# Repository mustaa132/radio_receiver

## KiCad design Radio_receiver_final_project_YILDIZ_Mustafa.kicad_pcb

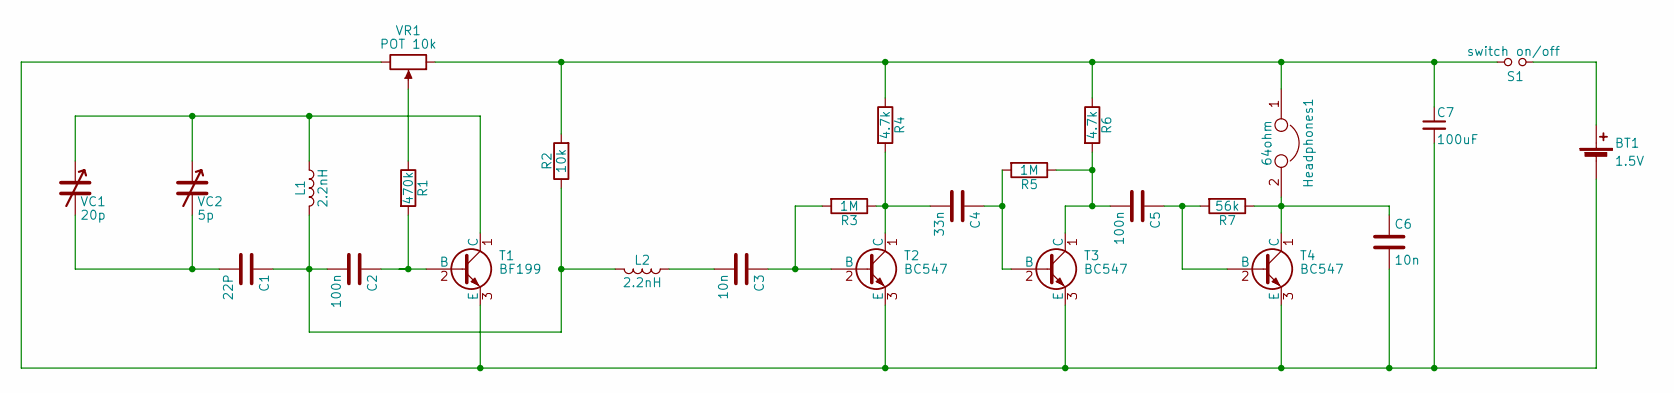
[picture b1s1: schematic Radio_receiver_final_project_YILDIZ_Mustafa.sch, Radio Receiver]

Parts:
BT1: 1.5V; WireConnection_2.50mmDrill
C1: 22P; C_1210_HandSoldering
C2: 100n; C_1206
C3, C6: 10n; C_Disc_D7.0mm_W2.5mm_P5.00mm
C4: 33n; C_Rect_L4.6mm_W3.0mm_P2.50mm_MKS02_FKP02
C5: 100n; C_Rect_L10.0mm_W3.0mm_P7.50mm_FKS3_FKP3
C7: 100uF; CP_Radial_D7.5mm_P2.50mm
Headphones1: 64ohm; RV_Disc_D7_W4_P5
L1, L2: 2.2nH; Neosid_Inductor_SM-PIC0602H
R1: 470k; R_Axial_DIN0309_L9.0mm_D3.2mm_P12.70mm_Horizontal
R2: 10k; R_Axial_DIN0207_L6.3mm_D2.5mm_P10.16mm_Horizontal
R3, R5: 1M; R_Axial_DIN0207_L6.3mm_D2.5mm_P10.16mm_Horizontal
R4, R6: 4.7k; R_Axial_DIN0207_L6.3mm_D2.5mm_P10.16mm_Horizontal
R7: 56k; R_Axial_DIN0207_L6.3mm_D2.5mm_P10.16mm_Horizontal
S1: switch on/off; WireConnection_1.50mmDrill
T1: BF199; TO-92_Molded_Narrow_Oval
T2, T4: BC547; TO-92_Molded_Narrow_Oval
T3: BC547; TO-92_Molded_Narrow
VC1: 20p; CP_Radial_Tantal_D4.5mm_P5.00mm
VC2: 5p; CP_Radial_Tantal_D5.0mm_P2.50mm
VR1: POT 10k; Potentiometer_Alps_RK097_Single_Vertical

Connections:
unnamed: BT1.1 (+), S1.1
unnamed: BT1.2 (-), C6.2, C7.2, T1.3 (E), T2.3 (E), T3.3 (E), T4.3 (E), VR1.3
unnamed: C1.1, C2.2, L1.2, L2.2, R2.1
unnamed: C1.2, VC1.2, VC2.2
unnamed: C2.1, R1.2, T1.2 (B)
unnamed: C3.1, R3.2, T2.2 (B)
unnamed: C3.2, L2.1
unnamed: C4.1, R5.2, T3.2 (B)
unnamed: C4.2, R3.1, R4.2, T2.1 (C)
unnamed: C5.1, R7.2, T4.2 (B)
unnamed: C5.2, R5.1, R6.2, T3.1 (C)
unnamed: C6.1, Headphones1.2, R7.1, T4.1 (C)
unnamed: C7.1, Headphones1.1, R2.2, R4.1, R6.1, S1.2, VR1.1
unnamed: L1.1, T1.1 (C), VC1.1, VC2.1
unnamed: R1.1, VR1.2

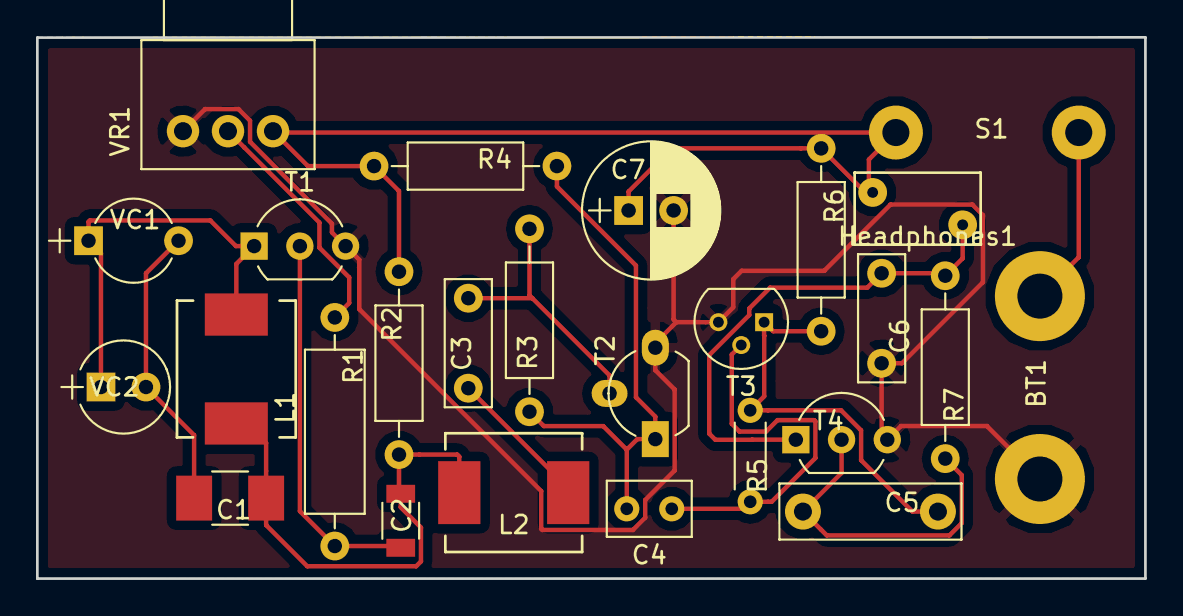
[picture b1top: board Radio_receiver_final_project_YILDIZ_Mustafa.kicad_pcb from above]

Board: 2 copper layers, 61.6 x 30.1 mm, 26 parts (0 on the bottom side), 15 nets.

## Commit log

2017-06-01 Radio_receiver_Final_Project_Mustafa_Yıldız
2017-06-13 some shanges
